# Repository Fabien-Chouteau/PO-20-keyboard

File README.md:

# PO-20-keyboard
Extra keyboard to play melody on the Pocket-Operator Arcade

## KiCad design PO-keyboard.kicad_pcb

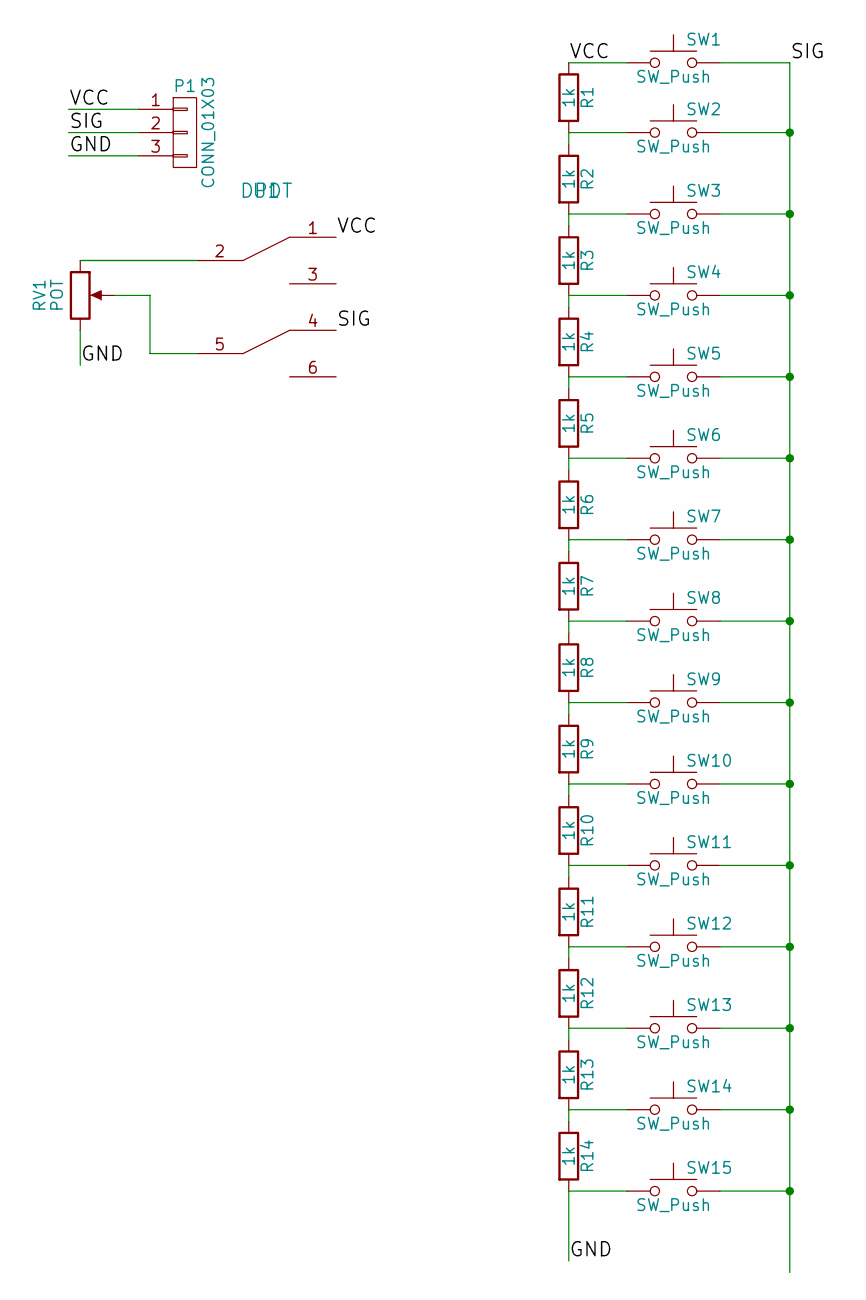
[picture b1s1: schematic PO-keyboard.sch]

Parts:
P1: CONN_01X03; Socket_Strip_Straight_1x03
R1, R2, R3, R4, R5, R6, R7, R8, R9, R10, R11, R12, R13, R14: 1k; R_0805_HandSoldering
RV1: POT; Potentiometer_WirePads_Small
SW1, SW2, SW3, SW4, SW5, SW6, SW7, SW8, SW9, SW10, SW11, SW12, SW13, SW14, SW15: SW_Push; SW_SPST_EVQQ2
U1: DPDT; SSSS922500

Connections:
/GND: P1.3, R14.2, RV1.3, SW15.1
/SIG: P1.2, SW1.2, SW2.2, SW3.2, SW4.2, SW5.2, SW6.2, SW7.2, SW8.2, SW9.2, SW10.2, SW11.2, SW12.2, SW13.2, SW14.2, SW15.2, U1.4
/VCC: P1.1, R1.1, SW1.1, U1.1
unnamed: R1.2, R2.1, SW2.1
unnamed: R2.2, R3.1, SW3.1
unnamed: R3.2, R4.1, SW4.1
unnamed: R4.2, R5.1, SW5.1
unnamed: R5.2, R6.1, SW6.1
unnamed: R6.2, R7.1, SW7.1
unnamed: R7.2, R8.1, SW8.1
unnamed: R8.2, R9.1, SW9.1
unnamed: R9.2, R10.1, SW10.1
unnamed: R10.2, R11.1, SW11.1
unnamed: R11.2, R12.1, SW12.1
unnamed: R12.2, R13.1, SW13.1
unnamed: R13.2, R14.1, SW14.1
unnamed: RV1.1, U1.2
unnamed: RV1.2, U1.5

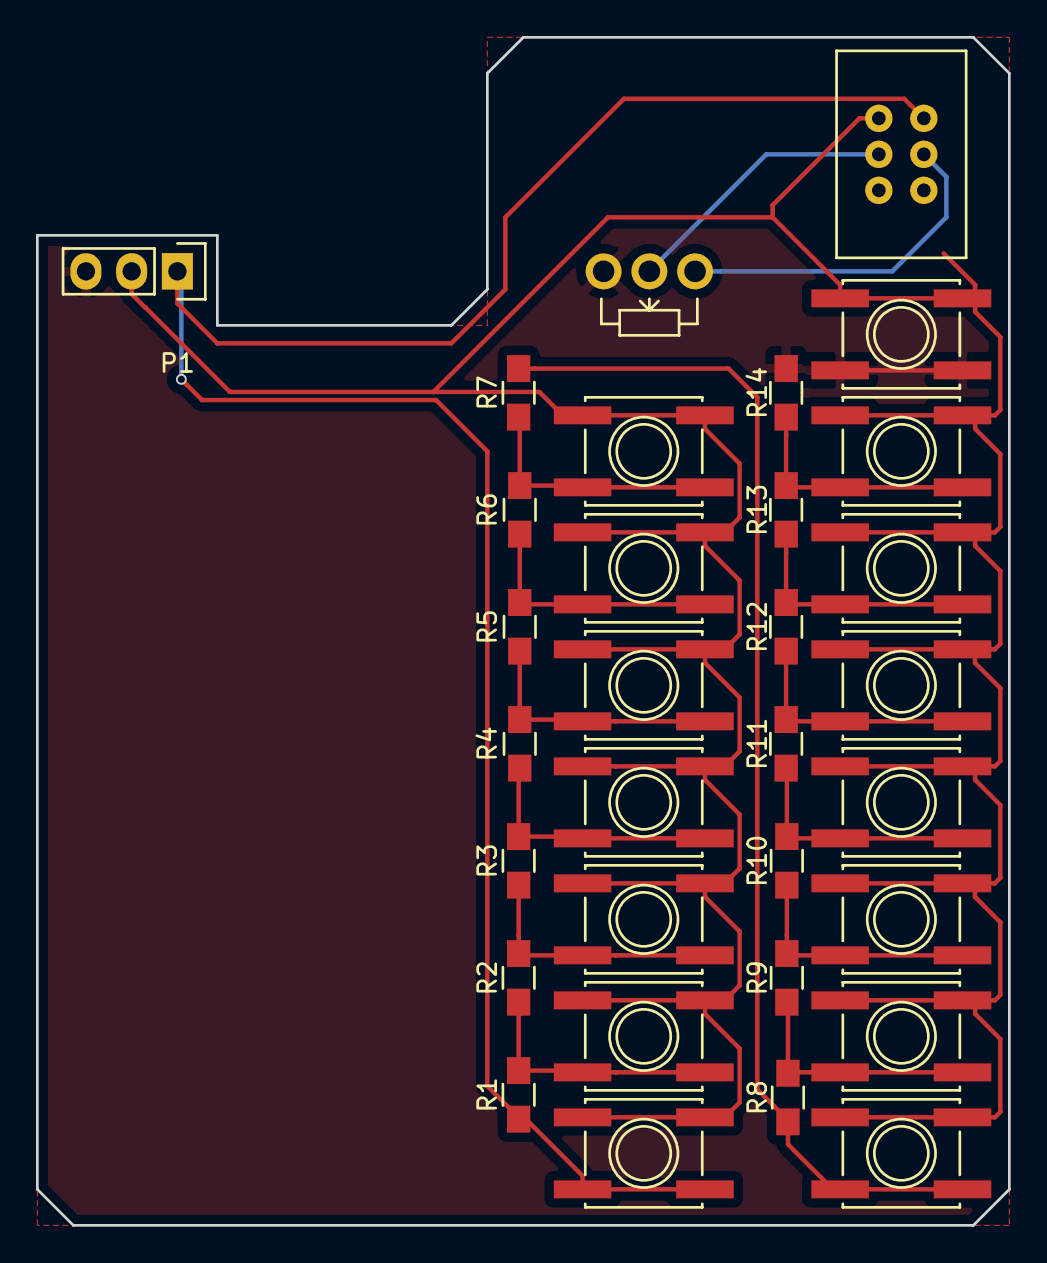
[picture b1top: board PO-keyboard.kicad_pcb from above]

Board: 2 copper layers, 54.0 x 66.0 mm, 32 parts (0 on the bottom side), 18 nets.

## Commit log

2017-04-21 First version of the keyboard
2017-04-21 Add 3D rendering
2017-05-08 Add gerber file for first version
